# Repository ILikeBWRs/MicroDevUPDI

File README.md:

Main project Page: [Here](https://github.com/ILikeBWRs/MicroDev128)

---

# MicroDevUPDI
 A UPDI programmer for the MicroDev128 Series. Compatible with most computers (Linux, Windows, Mac). Based on the CH340E USB to serial chip. This is a simple universal USBtoUDPI converter. 

 Designed on a two layer board feturing reverse polarity protection. Files included for KiCad 10. 

See Document Repo for technical specs: [Here](https://github.com/ILikeBWRs/MicroDev128-Documentation)

Thanks to PCBWay for sponsoring this project!

 ---

 For more information on ordering etc see the main project page. 

 ---

 Revision: *1A*

 Document Version: *1.00*

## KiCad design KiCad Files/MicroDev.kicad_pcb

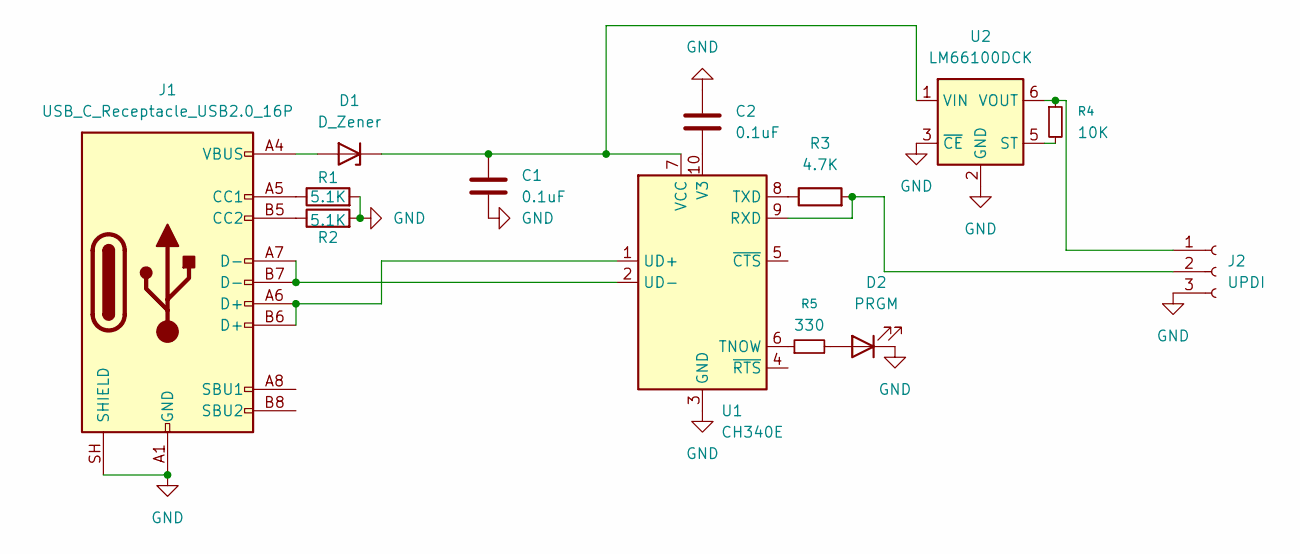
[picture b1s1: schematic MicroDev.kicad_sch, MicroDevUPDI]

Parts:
C1, C2: 0.1uF; C_0402_1005Metric
D1: D_Zener; D_SOD-123
D2: PRGM; LED_0603_1608Metric
J1: USB_C_Receptacle_USB2.0_16P; USB_C_Receptacle_HRO_TYPE-C-31-M-12
J2: UPDI; PinSocket_1x03_P2.54mm_Vertical
R1, R2: 5.1K; R_0402_1005Metric
R3: 4.7K; R_0402_1005Metric
R4: 10K; R_0402_1005Metric
R5: 330; R_0402_1005Metric
U1: CH340E; MSOP-10_3x3mm_P0.5mm
U2: LM66100DCK; SOT-363_SC-70-6

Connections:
GND: C1.2, C2.1, D2.1 (K), J1.A1 (GND), J1.A12 (GND), J1.B1 (GND), J1.B12 (GND), J1.SH (SHIELD), J2.3, R1.2, R2.2, U1.3 (GND), U2.2 (GND), U2.3 (~CE)
unnamed: D1.2 (A), J1.A4 (VBUS), J1.A9 (VBUS), J1.B4 (VBUS), J1.B9 (VBUS)
unnamed: C1.1, D1.1 (K), U1.7 (VCC), U2.1 (VIN)
unnamed: D2.2 (A), R5.2
unnamed: J1.A5 (CC1), R1.1
unnamed: J1.B5 (CC2), R2.1
unnamed: J2.1, R4.1, U2.6 (VOUT)
unnamed: J2.2, R3.2, U1.9 (RXD)
unnamed: R5.1, U1.6 (TNOW)
unnamed: R3.1, U1.8 (TXD)
unnamed: J1.A6 (D+), J1.B6 (D+), U1.1 (UD+)
unnamed: J1.A7 (D-), J1.B7 (D-), U1.2 (UD-)
unnamed: C2.2, U1.10 (V3)
unnamed: R4.2, U2.5 (ST)

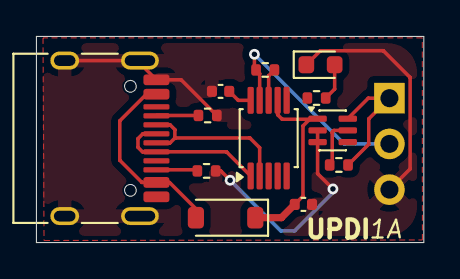
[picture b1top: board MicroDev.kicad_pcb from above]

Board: 2 copper layers, 21.5 x 11.5 mm, 13 parts (1 on the bottom side), 14 nets.

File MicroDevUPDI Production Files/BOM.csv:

Ref Des,Qty,Manufacturer,Mfg Part#,Description/Value,Package,Type,Notes
"C1,C2",2,Samsung Electro-Mechanics,CL05B104KO5NNNC,0.1uF Ceramic X7R Cap,402,SMD,
D1,1,JCET / Yongyutai / MSKSEMI,MBR0520,Schottky diode 20V 0.5A,SOD-123,SMD,Made by many manufacturers – sourcing is not strict
D2,1,Everlight,19-217/R6C-AL1M2VY/3T,Standard Red SMD Led,603,SMD,Any 0603 SMD LED – any colour works
J1,1,Korean Hroparts Elec,TYPE-C-31-M-12,16Pin USB-C connector,16Pin USB-C,SMD + THT,
J2,1, DNP,DNP,DNP,DNP,DNP,Do not populate
"R1,R2",2,Yageo,RC0402FR-075K1L,5.1K 1% 1/16W Metal film resistor,402,SMD,
R3,1,Yageo,RC0402FR-074K7L,4.7K 1% 1/16W Metal film resistor,402,SMD,
R4,1,Yageo,RC0402FR-0710KL,"10K, 1% 1/16W Metal film resistor",402,SMD,
R5,1,Yageo,RC0402FR-07330RL,330Ohm 1% 1/16W Metal film resistor,,,
U1,1,WCH,CH340E,"USB serial converter, UART",MSOP-10,SMD,"Must have dot aligned with the arrow, which indicates pin 1"
U2,1,"Texas Instruments
",LM66100DCKR,Ideal Diode With Input Polarity Protection, SC-70-6,SMD,"Must have dot aligned with the arrow, which indicates pin 1"
